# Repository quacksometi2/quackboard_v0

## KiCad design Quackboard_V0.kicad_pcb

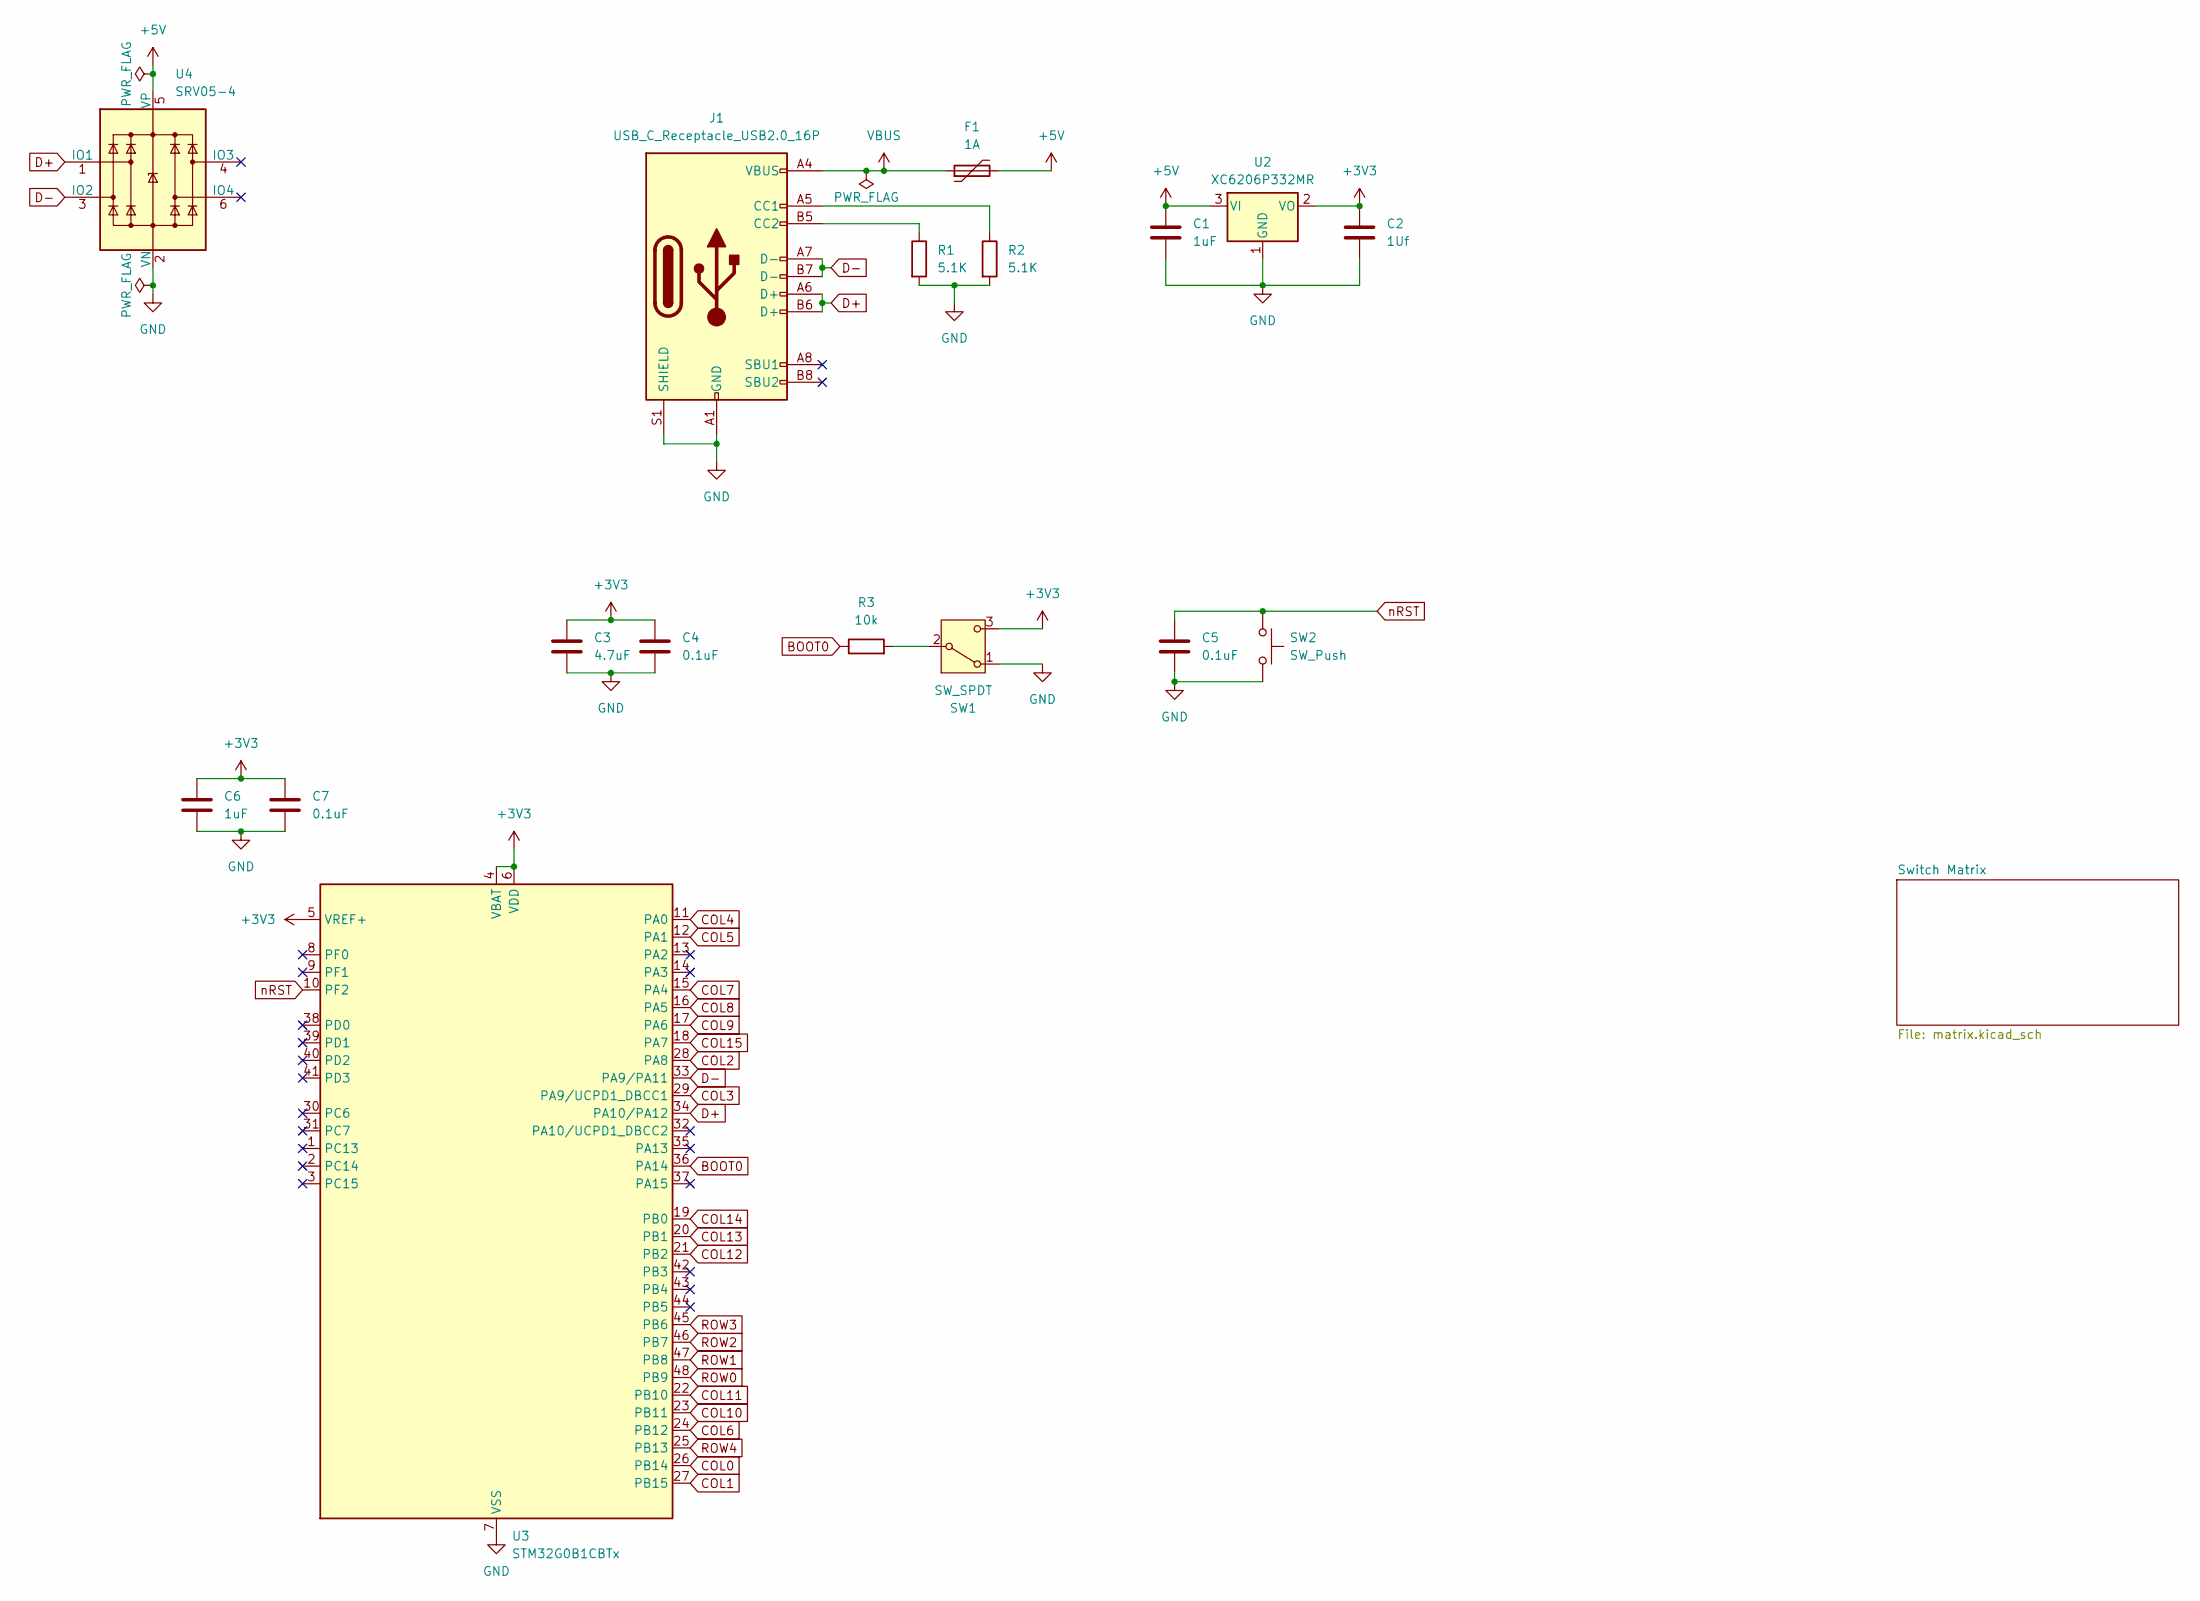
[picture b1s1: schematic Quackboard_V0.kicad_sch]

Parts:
C1, C6: 1uF; C_0805_2012Metric
C2: 1Uf; C_0805_2012Metric
C3: 4.7uF; C_0805_2012Metric
C4, C5, C7: 0.1uF; C_0805_2012Metric
F1: 1A; Fuse_1206_3216Metric
J1: USB_C_Receptacle_USB2.0_16P; USB_C_Receptacle_HRO_TYPE-C-31-M-12
R1, R2: 5.1K; R_0805_2012Metric
R3: 10k; R_0805_2012Metric
SW1: SW_SPDT; SW_Slide_SPDT_Straight_CK_OS102011MS2Q
SW2: SW_Push; SW_SPST_TL3342
U2: XC6206P332MR; SOT-23-3
U3: STM32G0B1CBTx; LQFP-48_7x7mm_P0.5mm
U4: SRV05-4; SOT-23-6

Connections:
+3V3: C2.1, C3.1, C4.1, C6.1, C7.1, SW1.3 (C), U2.2 (VO), U3.4 (VBAT), U3.5 (VREF+), U3.6 (VDD)
+5V: C1.1, F1.2, U2.3 (VI), U4.5 (VP)
BOOT0: R3.1, U3.36 (PA14)
COL0: U3.26 (PB14); also elsewhere on the board
COL1: U3.27 (PB15); also elsewhere on the board
COL2: U3.28 (PA8); also elsewhere on the board
COL3: U3.29 (PA9/UCPD1_DBCC1); also elsewhere on the board
COL4: U3.11 (PA0); also elsewhere on the board
COL5: U3.12 (PA1); also elsewhere on the board
COL6: U3.24 (PB12); also elsewhere on the board
COL7: U3.15 (PA4); also elsewhere on the board
COL8: U3.16 (PA5); also elsewhere on the board
COL9: U3.17 (PA6); also elsewhere on the board
COL10: U3.23 (PB11); also elsewhere on the board
COL11: U3.22 (PB10); also elsewhere on the board
COL12: U3.21 (PB2); also elsewhere on the board
COL13: U3.20 (PB1); also elsewhere on the board
COL14: U3.19 (PB0); also elsewhere on the board
COL15: U3.18 (PA7); also elsewhere on the board
D+: J1.A6 (D+), J1.B6 (D+), U3.34 (PA10/PA12), U4.1 (IO1)
D-: J1.A7 (D-), J1.B7 (D-), U3.33 (PA9/PA11), U4.3 (IO2)
GND: C1.2, C2.2, C3.2, C4.2, C5.2, C6.2, C7.2, J1.A1 (GND), J1.A12 (GND), J1.B1 (GND), J1.B12 (GND), J1.S1 (SHIELD), R1.2, R2.2, SW1.1 (A), SW2.2, U2.1 (GND), U3.7 (VSS), U4.2 (VN)
unnamed: J1.A5 (CC1), R2.1
unnamed: J1.B5 (CC2), R1.1
unnamed: R3.2, SW1.2 (B)
ROW0: U3.48 (PB9); also elsewhere on the board
ROW1: U3.47 (PB8); also elsewhere on the board
ROW2: U3.46 (PB7); also elsewhere on the board
ROW3: U3.45 (PB6); also elsewhere on the board
ROW4: U3.25 (PB13); also elsewhere on the board
VBUS: F1.1, J1.A4 (VBUS), J1.A9 (VBUS), J1.B4 (VBUS), J1.B9 (VBUS)
nRST: C5.1, SW2.1, U3.10 (PF2)

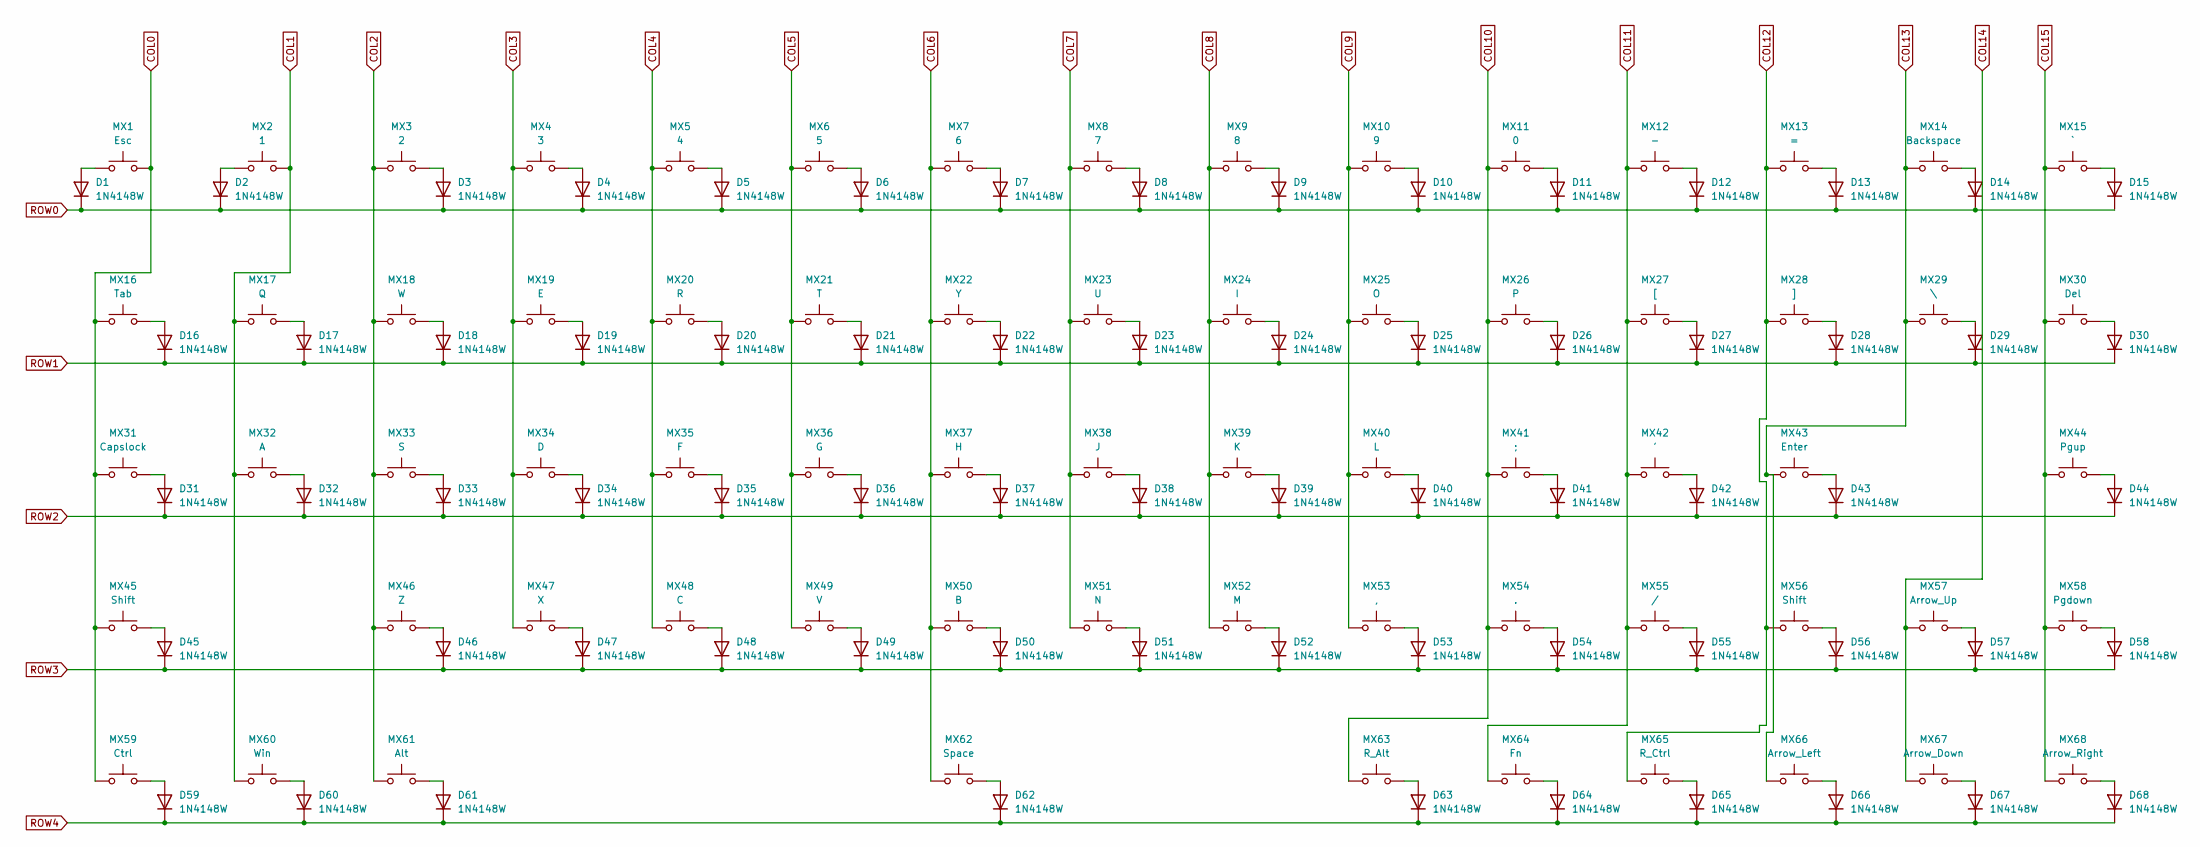
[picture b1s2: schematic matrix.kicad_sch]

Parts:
D1, D2, D3, D4, D5, D6, D7, D8, D9, D10, D11, D12, D13, D14, D15, D16, D17, D18, D19, D20, D21, D22, D23, D24, D25, D26, D27, D28, D29, D30, D31, D32, D33, D34, D35, D36, D37, D38, D39, D40, D41, D42, D43, D44, D45, D46, D47, D48, D49, D50, D51, D52, D53, D54, D55, D56, D57, D58, D59, D60, D61, D62, D63, D64, D65, D66, D67, D68: 1N4148W; D_SOD-123
MX1: Esc; MX-Hotswap-1U
MX2: 1; MX-Hotswap-1U
MX3: 2; MX-Hotswap-1U
MX4: 3; MX-Hotswap-1U
MX5: 4; MX-Hotswap-1U
MX6: 5; MX-Hotswap-1U
MX7: 6; MX-Hotswap-1U
MX8: 7; MX-Hotswap-1U
MX9: 8; MX-Hotswap-1U
MX10: 9; MX-Hotswap-1U
MX11: 0; MX-Hotswap-1U
MX12: -; MX-Hotswap-1U
MX13: =; MX-Hotswap-1U
MX14: Backspace; MX-Hotswap-2U
MX15: `; MX-Hotswap-1U
MX16: Tab; MX-Hotswap-1.5U
MX17: Q; MX-Hotswap-1U
MX18: W; MX-Hotswap-1U
MX19: E; MX-Hotswap-1U
MX20: R; MX-Hotswap-1U
MX21: T; MX-Hotswap-1U
MX22: Y; MX-Hotswap-1U
MX23: U; MX-Hotswap-1U
MX24: I; MX-Hotswap-1U
MX25: O; MX-Hotswap-1U
MX26: P; MX-Hotswap-1U
MX27: [; MX-Hotswap-1U
MX28: ]; MX-Hotswap-1U
MX29: \; MX-Hotswap-1.5U
MX30: Del; MX-Hotswap-1U
MX31: Capslock; MX-Hotswap-1.75U
MX32: A; MX-Hotswap-1U
MX33: S; MX-Hotswap-1U
MX34: D; MX-Hotswap-1U
MX35: F; MX-Hotswap-1U
MX36: G; MX-Hotswap-1U
MX37: H; MX-Hotswap-1U
MX38: J; MX-Hotswap-1U
MX39: K; MX-Hotswap-1U
MX40: L; MX-Hotswap-1U
MX41: ;; MX-Hotswap-1U
MX42: '; MX-Hotswap-1U
MX43: Enter; MX-Hotswap-2.25U
MX44: Pgup; MX-Hotswap-1U
MX45: Shift; MX-Hotswap-2.25U
MX46: Z; MX-Hotswap-1U
MX47: X; MX-Hotswap-1U
MX48: C; MX-Hotswap-1U
MX49: V; MX-Hotswap-1U
MX50: B; MX-Hotswap-1U
MX51: N; MX-Hotswap-1U
MX52: M; MX-Hotswap-1U
MX53: ,; MX-Hotswap-1U
MX54: .; MX-Hotswap-1U
MX55: /; MX-Hotswap-1U
MX56: Shift; MX-Hotswap-1.75U
MX57: Arrow_Up; MX-Hotswap-1U
MX58: Pgdown; MX-Hotswap-1U
MX59: Ctrl; MX-Hotswap-1.25U
MX60: Win; MX-Hotswap-1.25U
MX61: Alt; MX-Hotswap-1.25U
MX62: Space; MX-Hotswap-6.25U
MX63: R_Alt; MX-Hotswap-1U
MX64: Fn; MX-Hotswap-1U
MX65: R_Ctrl; MX-Hotswap-1U
MX66: Arrow_Left; MX-Hotswap-1U
MX67: Arrow_Down; MX-Hotswap-1U
MX68: Arrow_Right; MX-Hotswap-1U

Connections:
COL0: MX1.2, MX16.1, MX31.1, MX45.1, MX59.1; also elsewhere on the board
COL1: MX2.2, MX17.1, MX32.1, MX60.1; also elsewhere on the board
COL2: MX3.1, MX18.1, MX33.1, MX46.1, MX61.1; also elsewhere on the board
COL3: MX4.1, MX19.1, MX34.1, MX47.1; also elsewhere on the board
COL4: MX5.1, MX20.1, MX35.1, MX48.1; also elsewhere on the board
COL5: MX6.1, MX21.1, MX36.1, MX49.1; also elsewhere on the board
COL6: MX7.1, MX22.1, MX37.1, MX50.1, MX62.1; also elsewhere on the board
COL7: MX8.1, MX23.1, MX38.1, MX51.1; also elsewhere on the board
COL8: MX9.1, MX24.1, MX39.1, MX52.1; also elsewhere on the board
COL9: MX10.1, MX25.1, MX40.1, MX53.1; also elsewhere on the board
COL10: MX11.1, MX26.1, MX41.1, MX54.1, MX63.1; also elsewhere on the board
COL11: MX12.1, MX27.1, MX42.1, MX55.1, MX64.1; also elsewhere on the board
COL12: MX13.1, MX28.1, MX56.1, MX65.1; also elsewhere on the board
COL13: MX14.1, MX29.1, MX43.1, MX66.1; also elsewhere on the board
COL14: MX57.1, MX67.1; also elsewhere on the board
COL15: MX15.1, MX30.1, MX44.1, MX58.1, MX68.1; also elsewhere on the board
unnamed: D1.2 (A), MX1.1
unnamed: D2.2 (A), MX2.1
unnamed: D3.2 (A), MX3.2
unnamed: D4.2 (A), MX4.2
unnamed: D5.2 (A), MX5.2
unnamed: D6.2 (A), MX6.2
unnamed: D7.2 (A), MX7.2
unnamed: D8.2 (A), MX8.2
unnamed: D9.2 (A), MX9.2
unnamed: D10.2 (A), MX10.2
unnamed: D11.2 (A), MX11.2
unnamed: D12.2 (A), MX12.2
unnamed: D13.2 (A), MX13.2
unnamed: D14.2 (A), MX14.2
unnamed: D15.2 (A), MX15.2
unnamed: D16.2 (A), MX16.2
unnamed: D17.2 (A), MX17.2
unnamed: D18.2 (A), MX18.2
unnamed: D19.2 (A), MX19.2
unnamed: D20.2 (A), MX20.2
unnamed: D21.2 (A), MX21.2
unnamed: D22.2 (A), MX22.2
unnamed: D23.2 (A), MX23.2
unnamed: D24.2 (A), MX24.2
unnamed: D25.2 (A), MX25.2
unnamed: D26.2 (A), MX26.2
unnamed: D27.2 (A), MX27.2
unnamed: D28.2 (A), MX28.2
unnamed: D29.2 (A), MX29.2
unnamed: D30.2 (A), MX30.2
unnamed: D31.2 (A), MX31.2
unnamed: D32.2 (A), MX32.2
unnamed: D33.2 (A), MX33.2
unnamed: D34.2 (A), MX34.2
unnamed: D35.2 (A), MX35.2
unnamed: D36.2 (A), MX36.2
unnamed: D37.2 (A), MX37.2
unnamed: D38.2 (A), MX38.2
unnamed: D39.2 (A), MX39.2
unnamed: D40.2 (A), MX40.2
unnamed: D41.2 (A), MX41.2
unnamed: D42.2 (A), MX42.2
unnamed: D43.2 (A), MX43.2
unnamed: D44.2 (A), MX44.2
unnamed: D45.2 (A), MX45.2
unnamed: D46.2 (A), MX46.2
unnamed: D47.2 (A), MX47.2
unnamed: D48.2 (A), MX48.2
unnamed: D49.2 (A), MX49.2
unnamed: D50.2 (A), MX50.2
unnamed: D51.2 (A), MX51.2
unnamed: D52.2 (A), MX52.2
unnamed: D53.2 (A), MX53.2
unnamed: D54.2 (A), MX54.2
unnamed: D55.2 (A), MX55.2
unnamed: D56.2 (A), MX56.2
unnamed: D57.2 (A), MX57.2
unnamed: D58.2 (A), MX58.2
unnamed: D59.2 (A), MX59.2
unnamed: D60.2 (A), MX60.2
unnamed: D61.2 (A), MX61.2
unnamed: D62.2 (A), MX62.2
unnamed: D63.2 (A), MX63.2
unnamed: D64.2 (A), MX64.2
unnamed: D65.2 (A), MX65.2
unnamed: D66.2 (A), MX66.2
unnamed: D67.2 (A), MX67.2
unnamed: D68.2 (A), MX68.2
ROW0: D1.1 (K), D2.1 (K), D3.1 (K), D4.1 (K), D5.1 (K), D6.1 (K), D7.1 (K), D8.1 (K), D9.1 (K), D10.1 (K), D11.1 (K), D12.1 (K), D13.1 (K), D14.1 (K), D15.1 (K); also elsewhere on the board
ROW1: D16.1 (K), D17.1 (K), D18.1 (K), D19.1 (K), D20.1 (K), D21.1 (K), D22.1 (K), D23.1 (K), D24.1 (K), D25.1 (K), D26.1 (K), D27.1 (K), D28.1 (K), D29.1 (K), D30.1 (K); also elsewhere on the board
ROW2: D31.1 (K), D32.1 (K), D33.1 (K), D34.1 (K), D35.1 (K), D36.1 (K), D37.1 (K), D38.1 (K), D39.1 (K), D40.1 (K), D41.1 (K), D42.1 (K), D43.1 (K), D44.1 (K); also elsewhere on the board
ROW3: D45.1 (K), D46.1 (K), D47.1 (K), D48.1 (K), D49.1 (K), D50.1 (K), D51.1 (K), D52.1 (K), D53.1 (K), D54.1 (K), D55.1 (K), D56.1 (K), D57.1 (K), D58.1 (K); also elsewhere on the board
ROW4: D59.1 (K), D60.1 (K), D61.1 (K), D62.1 (K), D63.1 (K), D64.1 (K), D65.1 (K), D66.1 (K), D67.1 (K), D68.1 (K); also elsewhere on the board

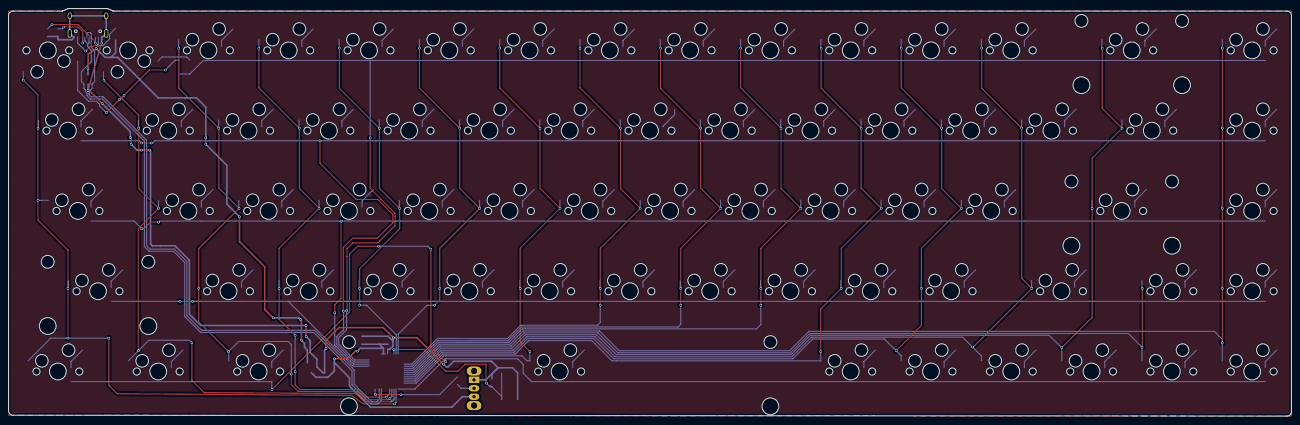
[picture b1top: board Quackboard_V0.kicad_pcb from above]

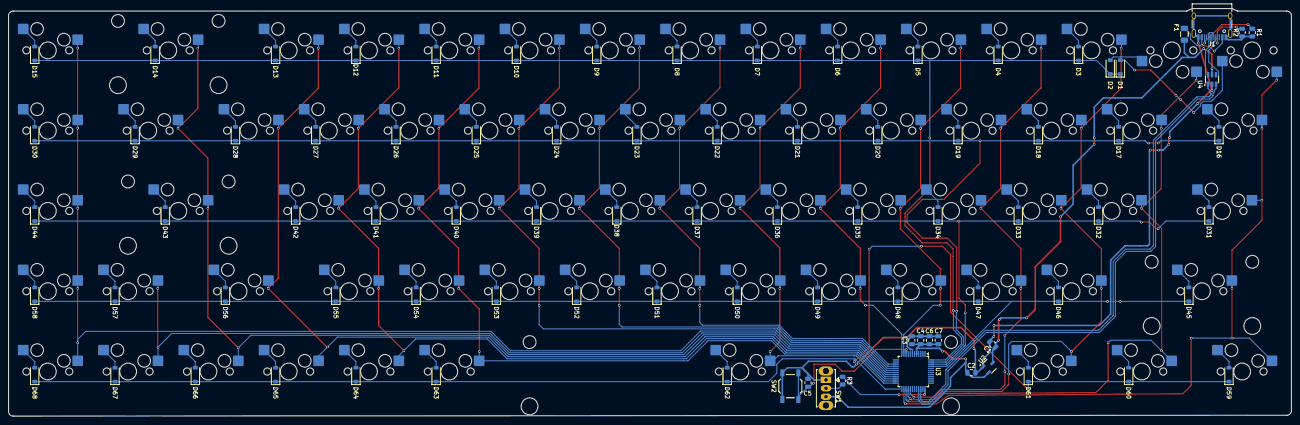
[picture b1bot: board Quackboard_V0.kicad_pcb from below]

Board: 2 copper layers, 304.4 x 96.7 mm, 153 parts (153 on the bottom side), 100 nets.

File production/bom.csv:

Designator,Footprint,Quantity,Value,LCSC Part #
"C1, C2, C6",805,3,1uF,
C3,805,1,4.7uF,
"C4, C5, C7",805,3,0.1uF,
"D1, D10, D11, D12, D13, D14, D15, D16, D17, D18, D19, D2, D20, D21, D22, D23, D24, D25, D26, D27, D28, D29, D3, D30, D31, D32, D33, D34, D35, D36, D37, D38, D39, D4, D40, D41, D42, D43, D44, D45, D46, D47, D48, D49, D5, D50, D51, D52, D53, D54, D55, D56, D57, D58, D59, D6, D60, D61, D62, D63, D64, D65, D66, D67, D68, D7, D8, D9",D_SOD-123,68,1N4148W,C81598
F1,1206,1,1A,
J1,USB_C_Receptacle_HRO_TYPE-C-31-M-12,1,USB_C_Receptacle_USB2.0_16P,
MX1,MX-Hotswap-1U,1,Esc,C41430893
MX10,MX-Hotswap-1U,1,9,C41430894
MX11,MX-Hotswap-1U,1,0,C41430895
MX12,MX-Hotswap-1U,1,-,C41430896
MX13,MX-Hotswap-1U,1,#ERROR!,C41430897
MX14,MX-Hotswap-2U,1,Backspace,C41430898
MX15,MX-Hotswap-1U,1,`,C41430899
MX16,MX-Hotswap-1.5U,1,Tab,C41430900
MX17,MX-Hotswap-1U,1,Q,C41430901
MX18,MX-Hotswap-1U,1,W,C41430902
MX19,MX-Hotswap-1U,1,E,C41430903
MX2,MX-Hotswap-1U,1,1,C41430904
MX20,MX-Hotswap-1U,1,R,C41430905
MX21,MX-Hotswap-1U,1,T,C41430906
MX22,MX-Hotswap-1U,1,Y,C41430907
MX23,MX-Hotswap-1U,1,U,C41430908
MX24,MX-Hotswap-1U,1,I,C41430909
MX25,MX-Hotswap-1U,1,O,C41430910
MX26,MX-Hotswap-1U,1,P,C41430911
MX27,MX-Hotswap-1U,1,[,C41430912
MX28,MX-Hotswap-1U,1,],C41430913
MX29,MX-Hotswap-1.5U,1,\,C41430914
MX3,MX-Hotswap-1U,1,2,C41430915
MX30,MX-Hotswap-1U,1,Del,C41430916
MX31,MX-Hotswap-1.75U,1,Capslock,C41430917
MX32,MX-Hotswap-1U,1,A,C41430918
MX33,MX-Hotswap-1U,1,S,C41430919
MX34,MX-Hotswap-1U,1,D,C41430920
MX35,MX-Hotswap-1U,1,F,C41430921
MX36,MX-Hotswap-1U,1,G,C41430922
MX37,MX-Hotswap-1U,1,H,C41430923
MX38,MX-Hotswap-1U,1,J,C41430924
MX39,MX-Hotswap-1U,1,K,C41430925
MX4,MX-Hotswap-1U,1,3,C41430926
MX40,MX-Hotswap-1U,1,L,C41430927
MX41,MX-Hotswap-1U,1,;,C41430928
MX42,MX-Hotswap-1U,1,,C41430929
MX43,MX-Hotswap-2.25U,1,Enter,C41430930
MX44,MX-Hotswap-1U,1,Pgup,C41430931
MX45,MX-Hotswap-2.25U,1,Shift,C41430932
MX46,MX-Hotswap-1U,1,Z,C41430933
MX47,MX-Hotswap-1U,1,X,C41430934
MX48,MX-Hotswap-1U,1,C,C41430935
MX49,MX-Hotswap-1U,1,V,C41430936
MX5,MX-Hotswap-1U,1,4,C41430937
MX50,MX-Hotswap-1U,1,B,C41430938
MX51,MX-Hotswap-1U,1,N,C41430939
MX52,MX-Hotswap-1U,1,M,C41430940
MX53,MX-Hotswap-1U,1,",",C41430941
MX54,MX-Hotswap-1U,1,.,C41430942
MX55,MX-Hotswap-1U,1,/,C41430943
MX56,MX-Hotswap-1.75U,1,Shift,C41430944
MX57,MX-Hotswap-1U,1,Arrow_Up,C41430945
MX58,MX-Hotswap-1U,1,Pgdown,C41430946
MX59,MX-Hotswap-1.25U,1,Ctrl,C41430947
MX6,MX-Hotswap-1U,1,5,C41430948
MX60,MX-Hotswap-1.25U,1,Win,C41430949
MX61,MX-Hotswap-1.25U,1,Alt,C41430950
MX62,MX-Hotswap-6.25U,1,Space,C41430951
MX63,MX-Hotswap-1U,1,R_Alt,C41430952
MX64,MX-Hotswap-1U,1,Fn,C41430953
MX65,MX-Hotswap-1U,1,R_Ctrl,C41430954
MX66,MX-Hotswap-1U,1,Arrow_Left,C41430955
MX67,MX-Hotswap-1U,1,Arrow_Down,C41430956
MX68,MX-Hotswap-1U,1,Arrow_Right,C41430957
MX7,MX-Hotswap-1U,1,6,C41430958
MX8,MX-Hotswap-1U,1,7,C41430959
MX9,MX-Hotswap-1U,1,8,C41430960
"R1, R2",805,2,5.1K,
R3,805,1,10k,
SW1,SW_Slide_SPDT_Straight_CK_OS102011MS2Q,1,SW_SPDT,C2939726
SW2,SW_SPST_TL3342,1,SW_Push,C318884
U2,SOT-23-3,1,XC6206P332MR,
U3,LQFP-48_7x7mm_P0.5mm,1,STM32G0B1CBTx,C81720
U4,SOT-23-6,1,SRV05-4,C85364

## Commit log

2026-01-21 Add a keyswitch submodule
2026-01-23 updated all files
